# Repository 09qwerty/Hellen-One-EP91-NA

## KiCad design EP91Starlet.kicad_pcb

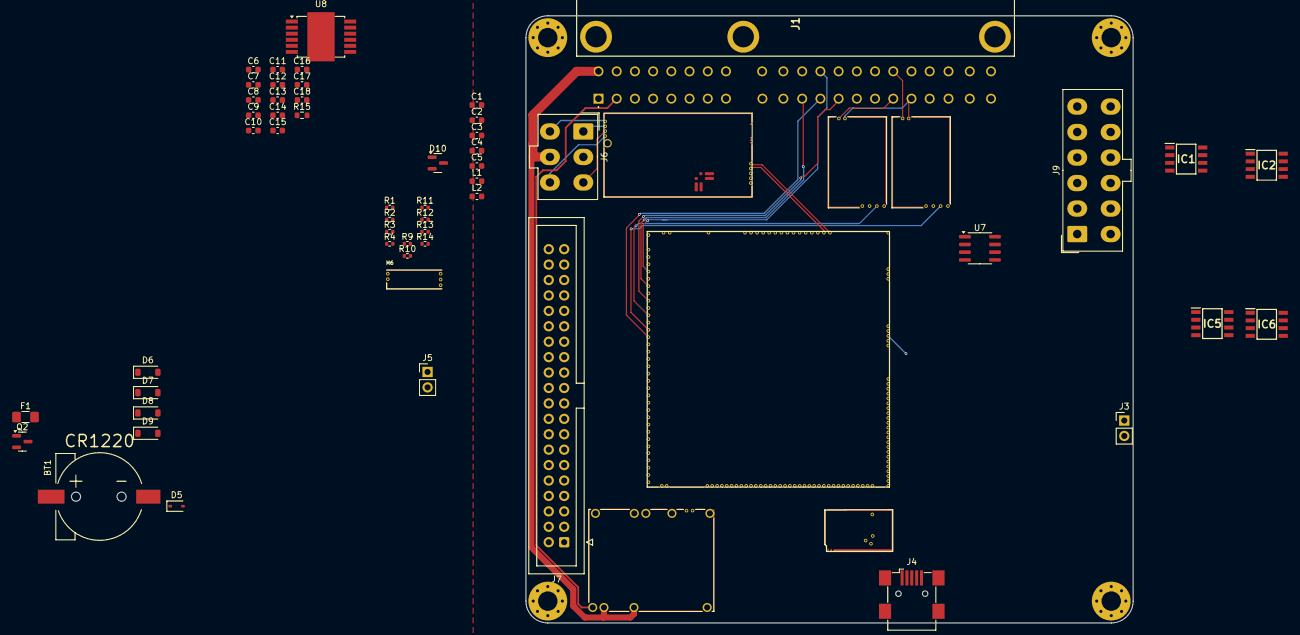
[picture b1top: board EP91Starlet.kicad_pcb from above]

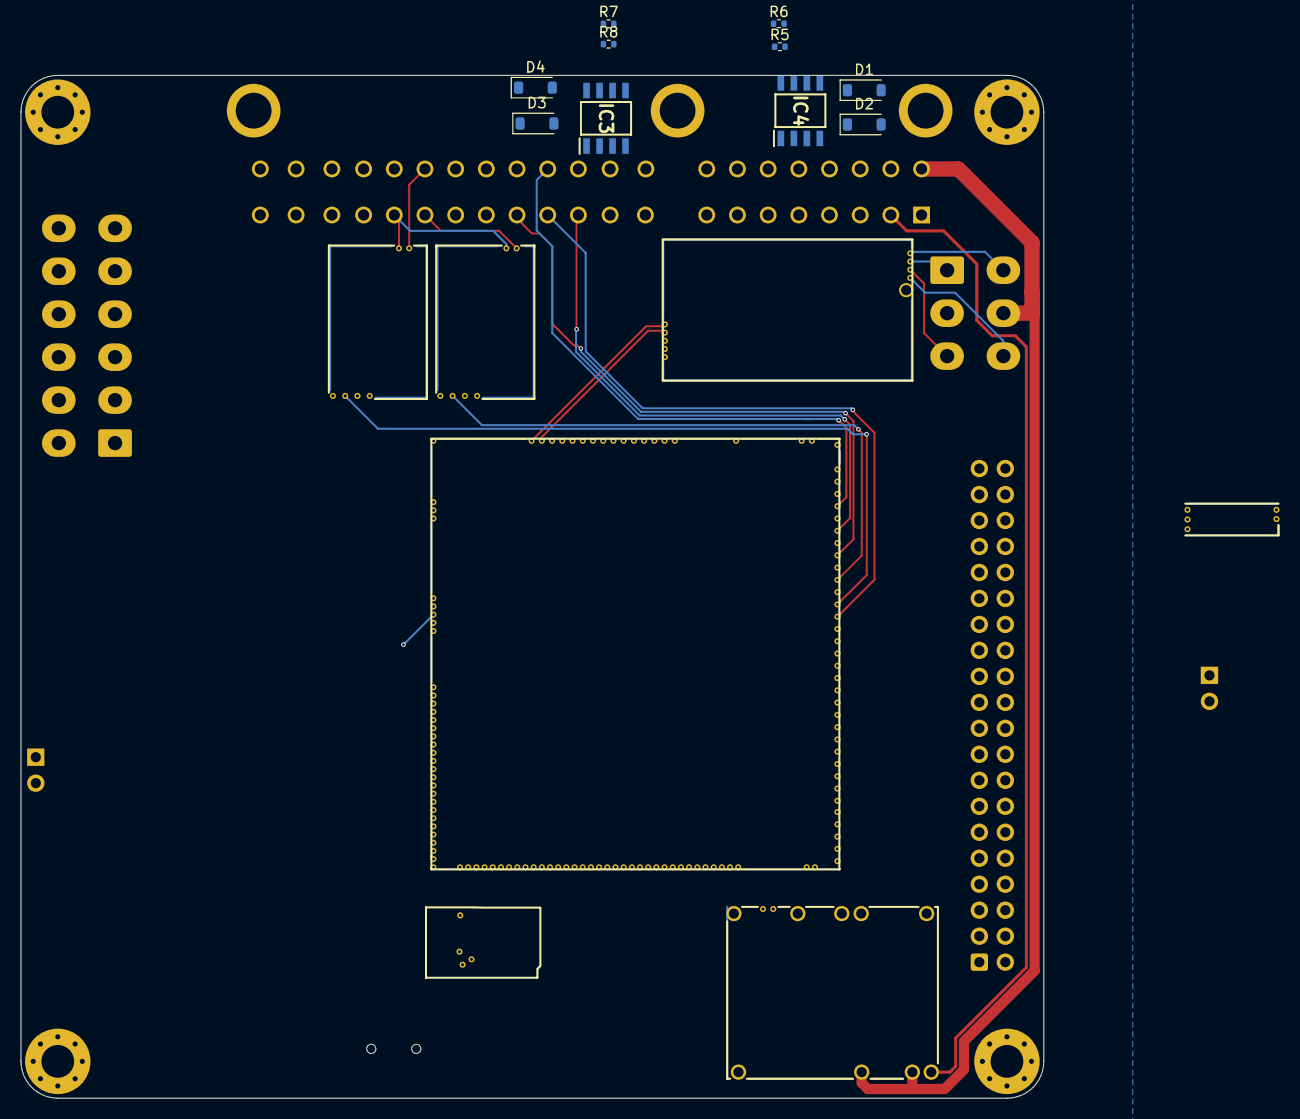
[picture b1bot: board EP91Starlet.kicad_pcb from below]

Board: 4 copper layers, 100.0 x 100.0 mm, 70 parts (10 on the bottom side), 109 nets.

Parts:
BT1: CR1220; CR1220-2
C1, C3, C17, C18: 10n; C_0603_1608Metric
C2, C4, C16: 100n; C_0603_1608Metric
C5: 1u; C_0603_1608Metric
C6, C7, C8, C9, C10, C11, C12, C13, C14, C15: 10u; C_0603_1608Metric
D1, D2, D3, D4, D6, D7, D8, D9: B5819W; D_SOD-123
D5: 1N4148WS; D_SOD-323
D10: NUP2105L; SOT-23
F1: Fuse; Fuse_1206_3216Metric_Pad1.42x1.75mm_HandSolder
IC1, IC2, IC3, IC4, IC5, IC6: VNLD5160-E; SOIC127P600X175-8N
J1: 175446-6; 1754466
J3, J5: Conn_01x02; PinHeader_1x02_P2.54mm_Vertical
J4: USB_B_Mini; USB_Mini-B_Wuerth_65100516121_Horizontal
J6: Conn_02x03_Top_Bottom; Molex_Mini-Fit_Jr_5566-06A_2x03_P4.20mm_Vertical
J7: Conn_02x20_Odd_Even; IDC-Header_2x20_P2.54mm_Vertical
J9: Conn_02x06_Top_Bottom; Molex_Mini-Fit_Jr_5566-12A_2x06_P4.20mm_Vertical
L1, L2: 470R@100MHz; L_0603_1608Metric
M1: Module-mega-mcu144-0.7; mega-mcu144
M2: Module-vr-max9924-0.1; vr-max9924
M3: Module-vr-discrete-0.5; vr-discrete
M4: Module-power_12and5V-0.3; power_12and5V
M5: Module-wbo-0.6; wbo
M6: Module-knock-0.2; knock
M7: Module-can-0.1; can
Q2: BSS138; SOT-23
R1, R2, R3, R4, R5, R6, R7, R8, R11, R12, R13, R14: 4.7k; R_0402_1005Metric
R9: 10k; R_0402_1005Metric
R10: 510R; R_0402_1005Metric
R15: 4.7k; R_0603_1608Metric
U7: MAX31855KASA; SOIC-8_3.9x4.9mm_P1.27mm
U8: TLE9201SG; Infineon_PG-DSO-12-11

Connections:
+3.3V: M1.N22 (V33), M1.N32 (V33), R15.2, U8.2 (VSO)
+3.3VA: C4.2, C5.2, M1.N28 (V33_SWITCHABLE), M7.V2 (CAN_VIO), U7.4 (V_CC)
+5V: M1.N31 (VCC), M4.E4 (V5)
+5VA: M1.E38 (V5A_SWITCHABLE), M1.N30 (V5A_SWITCHABLE), M1.W2 (V5A_SWITCHABLE), M2.E4 (V5_IN), M3.E4 (V5_IN), M5.W1 (V5_IN), M6.E1 (V5A), M7.V1 (V5)
+5VP: J1.118 (VCC), J7.10, J7.12, J7.14, J7.16, M4.V4 (5VP)
+12V_PERM: J1.2 (BATT), M4.V1 (V12_PERM)
+12V_RAW: D1.1 (K), D2.1 (K), D3.1 (K), D4.1 (K), D6.1 (K), D7.1 (K), D8.1 (K), D9.1 (K), F1.1, J1.9 (+B), J6.5, M4.V2 (IN_VIGN), M4.V3 (V12_RAW)
/5V_OUT1: J7.34, M1.W10 (IGN2)
/5V_OUT2: J7.32, M1.W9 (IGN3)
/5V_OUT3: J7.30, M1.W8 (IGN4)
/5V_OUT4: J7.28, M1.W7 (IGN5)
/5V_OUT5: J7.26, M1.W6 (IGN6)
/AIR: J1.105 (THA), M1.S26 (IN_IAT)
/AT1: J7.33, M1.S27 (IN_AT1)
/AT2: J7.35, M1.S29 (IN_AT2)
/AUX1: J7.23, M1.S13 (IN_AUX1)
/AUX2: J7.21, M1.S12 (IN_AUX2)
/AUX3: J7.19, M1.S11 (IN_AUX3)
/AUX4: J7.17, M1.S10 (IN_AUX4)
/CAM: M1.S24 (IN_CAM), M3.E3 (OUT)
/CAN1+: J7.18, M1.W12 (CANH), M5.W4 (CANH)
/CAN1-: J7.20, M1.W13 (CANL), M5.W3 (CANL)
/CAN2+: J7.38, M7.S1 (CANL)
/CAN2-: J7.36, M7.S2 (CANH)
/CHECKENGINE_IN: M1.E12 (OUT_IO2), R10.2
/CHECKENGINE_OUT: J1.10 (W), Q2.3 (D)
/COOLANT: J1.103 (THW), M1.S28 (IN_CLT)
/CRANK: M1.S22 (IN_CRANK), M2.E3 (OUT)
/D1_IN: J7.7, M1.S4 (IN_D1)
/D2_IN: J7.5, M1.S3 (IN_D2)
/D3_IN: J7.3, M1.S2 (IN_D3)
/D4_IN: J7.1, M1.S1 (IN_D4)
/DC1+: C18.2, J9.11, U8.7 (OUT2)
/DC1-: C17.2, J9.12, U8.5 (OUT1)
/DC Driver 1/DIR: M1.E6 (OUT_IO3), U8.1 (DIR)
/DC Driver 1/DIS: M1.E7 (OUT_IO5), R15.1, U8.11 (DIS)
/DC Driver 1/PWM: M1.E28 (OUT_PWM8), U8.12 (PWM)
/DC Driver 1/PWR: C6.2, C7.2, C8.2, C9.2, C10.2, C11.2, C12.2, C13.2, C14.2, C15.2, C16.2, F1.2, U8.4 (VS)
/EGT/SPI_CS: M1.N10 (SPI3_CS), U7.6 (~CS)
/EGT/SPI_SCK: M1.N11 (SPI3_SCK), U7.5 (SCK)
/EGT/SPI_SO: M1.N12 (SPI3_MISO), U7.7 (SO)
/EGT/T+: J3.1, L1.1
/EGT/T-: J3.2, L2.1
/FANRELAY_IN: IC4.3 (IN2), M1.E21 (OUT_IO4), R5.1
/FANRELAY_OUT: D2.2 (A), IC4.8 (DRAIN1), J1.120 (FAN)
/FUELRELAY_IN: IC4.1 (IN1), M1.E8 (OUT_IO1), R6.1
/FUELRELAY_OUT: D1.2 (A), IC4.6 (DRAIN2), J1.4 (FC)
/IACCLOSE_IN: IC3.1 (IN1), M1.E27 (OUT_PWM1), R8.1
/IACCLOSE_OUT: D4.2 (A), IC3.8 (DRAIN1), J1.101 (RSC)
/IACOPEN_IN: IC3.3 (IN2), M1.E17 (OUT_PWM2), R7.1
/IACOPEN_OUT: D3.2 (A), IC3.6 (DRAIN2), J1.114 (RSO)
/KNOCK_PROCESSED: M1.S23 (IN_KNOCK), M6.E3 (OUT_KNOCK)
/LS1_HOT_IN: IC6.1 (IN1), M1.E19 (OUT_INJ1), R1.1
/LS1_HOT_OUT: IC6.8 (DRAIN1), J1.125 (#20), J9.6
/LS1_IN: IC2.1 (IN1), M1.E31 (OUT_INJ5), R12.1
/LS1_OUT: D7.2 (A), IC2.8 (DRAIN1), J9.9
/LS2_HOT_IN: IC6.3 (IN2), M1.E18 (OUT_INJ2), R2.1
/LS2_HOT_OUT: IC6.6 (DRAIN2), J1.112 (#10), J9.5
/LS2_IN: IC2.3 (IN2), M1.E32 (OUT_INJ6), R11.1
/LS2_OUT: D6.2 (A), IC2.6 (DRAIN2), J9.10
/LS3_HOT_IN: IC5.1 (IN1), M1.E29 (OUT_INJ3), R4.1
/LS3_HOT_OUT: IC5.8 (DRAIN1), J9.4
/LS3_IN: IC1.1 (IN1), M1.E33 (OUT_INJ7), R14.1
/LS3_OUT: D9.2 (A), IC1.8 (DRAIN1), J9.7
/LS4_HOT_IN: IC5.3 (IN2), M1.E30 (OUT_INJ4), R3.1
/LS4_HOT_OUT: IC5.6 (DRAIN2), J9.3
/LS4_IN: IC1.3 (IN2), M1.E34 (OUT_INJ8), R13.1
/LS4_OUT: D8.2 (A), IC1.6 (DRAIN2), J9.8
/MAP: J1.104 (PIM), M1.S21 (IN_MAP1)
/MAP2: J7.31, M1.S20 (IN_MAP2)
/MAP3: J7.29, M1.S19 (IN_MAP3)
/O2S2: J7.27, M1.S15 (IN_O2S2)
/O2SENS: J1.110 (OX), M1.S16 (IN_O2S)
/PG: M1.N13 (SPI3_MOSI), M4.E6 (PG_5VP)
/PPS: J7.37, M1.S31 (IN_PPS)
/PPS2: J7.40, M1.S33 (IN_PPS2)
/PWR_EN: M1.N29 (OUT_PWR_EN), M4.E5 (EN_5VP)
/SENS1: J7.15, M1.S9 (IN_SENS1)
/SENS2: J7.13, M1.S8 (IN_SENS2)
/SENS3: J7.11, M1.S7 (IN_SENS3)
/SENS4: J7.9, M1.S6 (IN_SENS4)
/SPARK: J1.106 (IGT), M1.W11 (IGN1)
/THRESH: M1.E14 (OUT_PWM5), M3.E1 (Thresh_IN)
/TPS: J1.117 (PSW), M1.S30 (IN_TPS)
/TPS2: J7.39, M1.S32 (IN_TPS2)
/USB+: J4.1 (VBUS), M1.N4 (VBUS)
/VBAT: D5.1 (K), M1.N27 (VBAT), M4.E1 (VBAT)
/VIGN: M1.N26 (IN_VIGN), M4.E3 (VIGN)
/VR-: J1.109 (NE-), M2.W1 (VR-/HALL), M3.W1 (VR-)
/VRCAM+: J1.108 (I0F/G2), M3.W2 (VR+)
/VRCRANK+: J1.121 (NE), M2.W2 (VR+)
/VREF_KNOCK: M1.S5 (VREF2), M6.W2 (VREF)
/VSS: J1.13 (SPD), M1.S25 (IN_VSS)
GND: BT1.2 (-), C1.1, C3.1, C4.1, C5.1, C6.1, C7.1, C8.1, C9.1, C10.1, C11.1, C12.1, C13.1, C14.1, C15.1, C16.1, C17.1, C18.1, D10.3 (A), IC1.5 (SOURCE2), IC1.7 (SOURCE1), IC2.5 (SOURCE2), IC2.7 (SOURCE1), IC3.5 (SOURCE2), IC3.7 (SOURCE1), IC4.5 (SOURCE2), IC4.7 (SOURCE1), IC5.5 (SOURCE2), IC5.7 (SOURCE1), IC6.5 (SOURCE2), IC6.7 (SOURCE1), J1.113 (E01), J1.124 (E1), J1.MH1, J1.MH2, J1.MH3, J4.5 (GND), J4.6 (Shield), J5.2, J7.6, J7.8, J9.1, J9.2, M1.G (GND), M2.G (GND), M3.G (GND), M4.S1 (GND), M5.G (GND), M6.E2 (GND), M7.E1 (GND), Q2.2 (S), R1.2, R2.2, R3.2, R4.2, R5.2, R6.2, R7.2, R8.2, R9.2, R11.2, R12.2, R13.2, R14.2, U7.1 (GND), U8.6 (GND), U8.8 (SI), U8.9 (CSN), U8.10 (SCK), U8.13 (GND)
GNDA: J1.116 (E2), J7.2, J7.4, M1.E39 (GNDA), M1.W1 (GNDA)
unnamed: BT1.1 (+), D5.2 (A)
unnamed: J4.3 (D+), M1.N3 (USBP)
unnamed: J4.2 (D-), M1.N2 (USBM)
unnamed: J5.1, M6.W1 (IN_KNOCK)
unnamed: J6.1, M5.E4 (LSU_Rtrim)
unnamed: J6.2, M5.E5 (LSU_Htr)
unnamed: J6.3, M5.E3 (LSU_Ip)
unnamed: J6.4, M5.E1 (LSU_Un)
unnamed: J6.6, M5.E2 (LSU_Vm)
unnamed: M1.E4 (SPI2_CS/CAN2_RX), M7.V5 (CAN_TX)
unnamed: M1.E1 (SPI2_SCK/CAN2_TX), M7.V6 (CAN_RX)
unnamed: Q2.1 (G), R9.1, R10.1
unnamed: C2.2, C3.2, D10.2 (K), L1.2, U7.3 (T+)
unnamed: C1.2, C2.1, D10.1 (K), L2.2, U7.2 (T-)

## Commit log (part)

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2025-06-25 import previous kicad project
2025-06-25 progress
2025-06-25 inj wiring
2025-06-27 start pcb routing
2025-06-27 [skip actions] Auto-generated board v2.1
2025-06-27 JLC test
2025-06-27 pcb layouting
2025-06-27 fix drill origin
2025-06-29 add tps pinout png
2026-06-09 sync
